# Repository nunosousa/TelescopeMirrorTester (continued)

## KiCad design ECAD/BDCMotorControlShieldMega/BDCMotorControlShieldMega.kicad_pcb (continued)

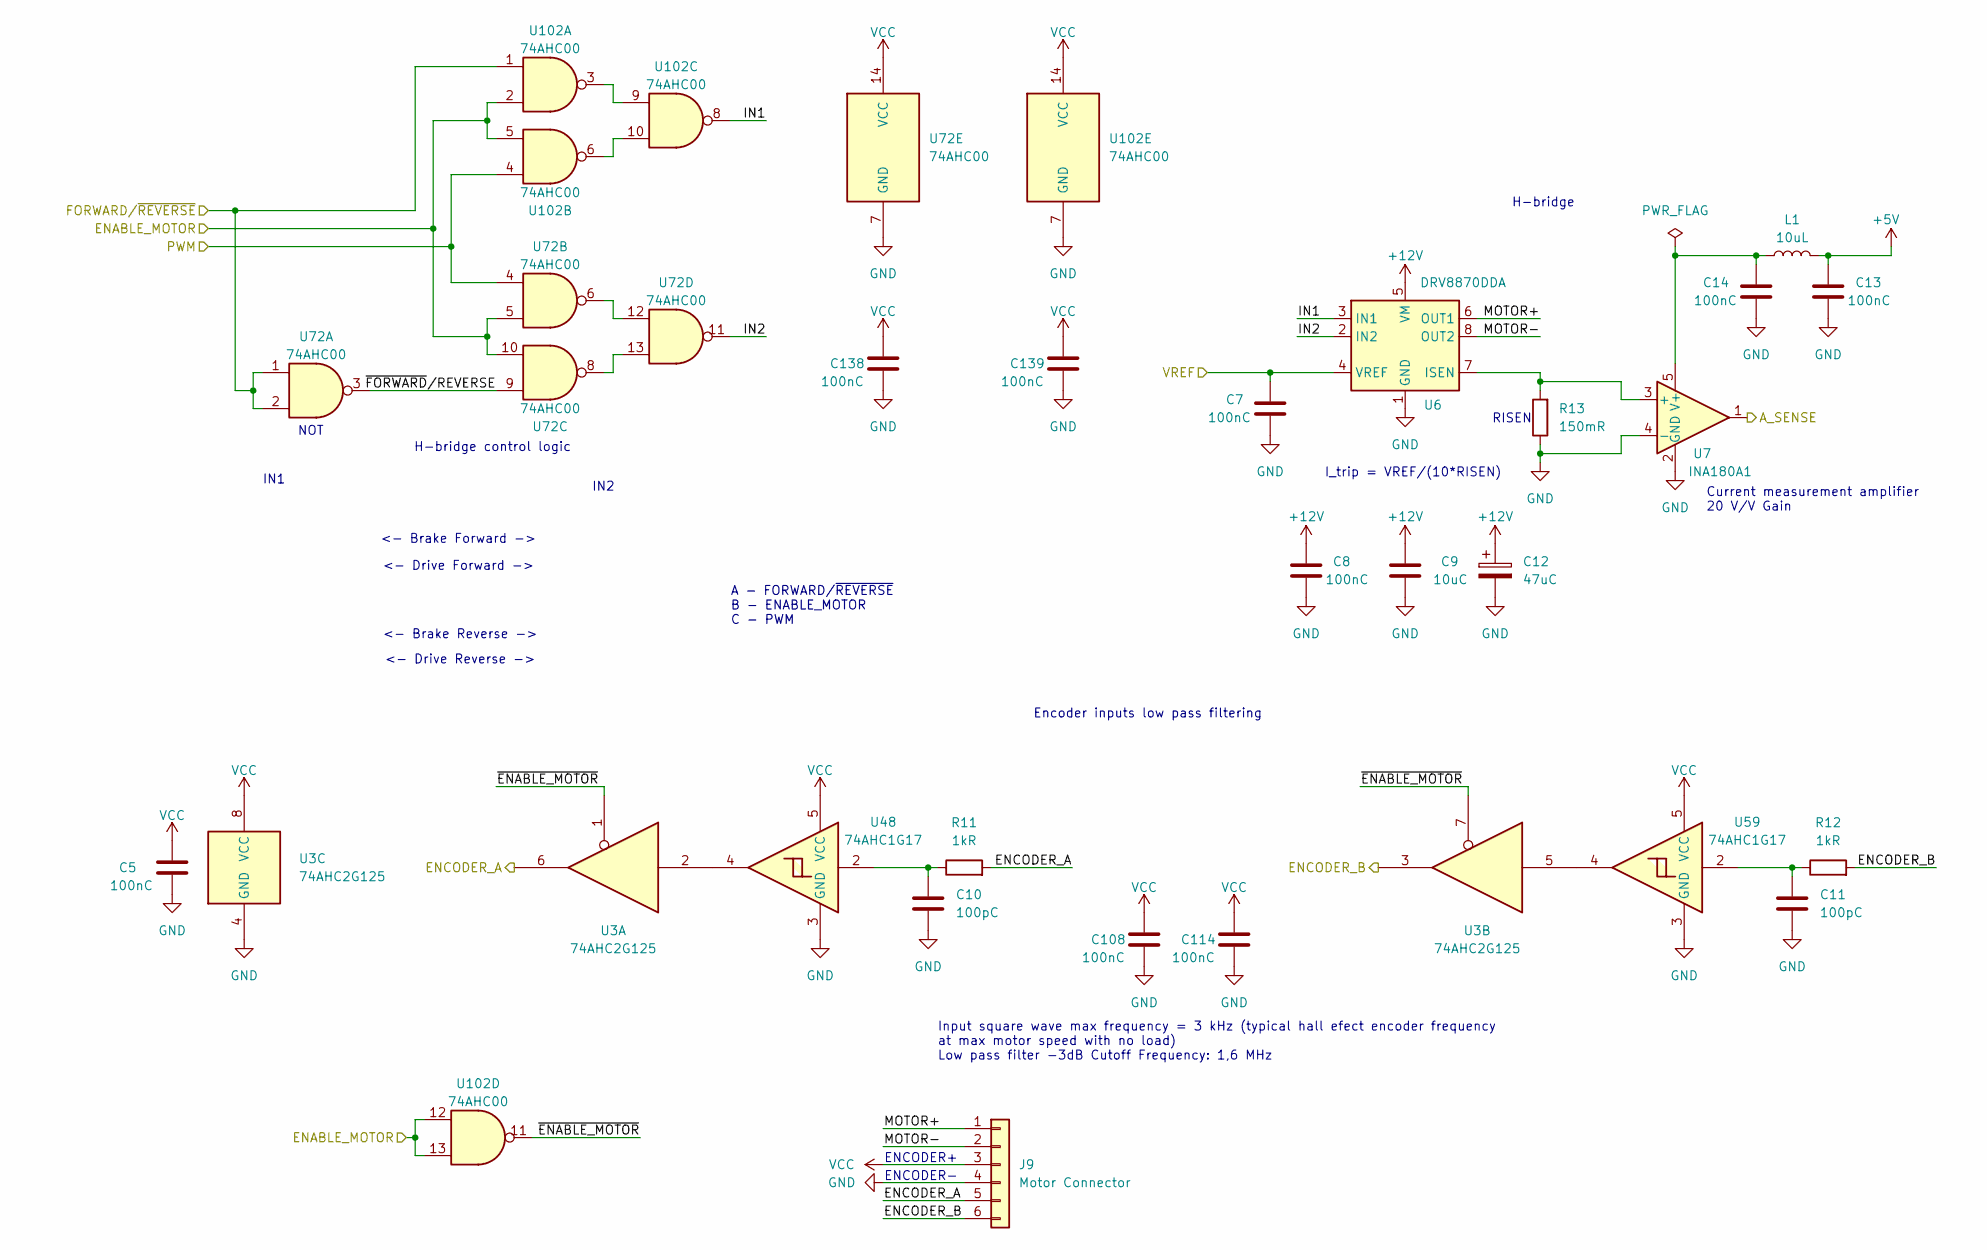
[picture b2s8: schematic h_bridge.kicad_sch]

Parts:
C5, C7, C8, C13, C14, C108, C114, C138, C139: 100nC; C_0805_2012Metric
C9: 10uC; C_1210_3225Metric; MPN UMK325AB7106KM-T
C10, C11: 100pC; C_0805_2012Metric; MPN CC0805KRX7R9BB101
C12: 47uC; CP_Radial_D5.0mm_P2.00mm; MPN 35YXJ47M5X11
J9: Motor Connector; JST_PH_B6B-PH-K_1x06_P2.00mm_Vertical; MPN B6B-PH-K-S(LF)(SN)
L1: 10uL; L_0805_2012Metric; MPN LQM21FN100M80L
R11, R12: 1kR; R_0805_2012Metric; MPN AC0805FR-7W1KL
R13: 150mR; R_1206_3216Metric; MPN RLH12FTCR150
U3: 74AHC2G125; TSSOP-8_3x3mm_P0.65mm; MPN 74AHC2G125DP,125
U6: DRV8870DDA; Texas_HTSOP-8-1EP_3.9x4.9mm_P1.27mm_EP2.95x4.9mm_Mask2.4x3.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; MPN DRV8870DDAR
U7: INA180A1; SOT-23-5; MPN INA180A1IDBVR
U48, U59: 74AHC1G17; SC-74A-5_1.55x2.9mm_P0.95mm; MPN 74AHC1G17GVH
U72, U102: 74AHC00; TSSOP-14_4.4x5mm_P0.65mm; MPN SN74AHC00PWR

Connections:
+5V: C13.1, L1.1; also elsewhere on the board
+12V: C8.1, C9.1, C12.1, U6.5 (VM); also elsewhere on the board
/*6: J9.6, R12.2, U3.3; also elsewhere on the board
/*7: J9.5, R11.2, U3.6; also elsewhere on the board
/*11: U72.4, U102.4; also elsewhere on the board
/Motor Control/CURRENT_M1A: U7.1; also elsewhere on the board
/Motor Control/EN_M1A: U72.5, U72.10, U102.2, U102.5, U102.12, U102.13; also elsewhere on the board
/Motor Control/F/~R_MA: U72.1, U72.2, U102.1; also elsewhere on the board
/Motor Control/H-bridge #1/IN1: U6.3 (IN1), U102.8
/Motor Control/H-bridge #1/IN2: U6.2 (IN2), U72.11
/Motor Control/H-bridge #1/MOTOR+: J9.1, U6.6 (OUT1)
/Motor Control/H-bridge #1/MOTOR-: J9.2, U6.8 (OUT2)
/Motor Control/H-bridge #1/~ENABLE_MOTOR: U3.1, U3.7, U102.11
/Motor Control/H-bridge #1/~FORWARD/REVERSE: U72.3, U72.9
/Motor Control/VREF_M1A: C7.1, U6.4 (VREF); also elsewhere on the board
GND: C5.2, C7.2, C8.2, C9.2, C10.2, C11.2, C12.2, C13.2, C14.2, C108.2, C114.2, C138.2, C139.2, J9.4, R13.1, U3.4 (GND), U6.1 (GND), U6.9 (GND), U7.2 (GND), U7.4 (-), U48.3 (GND), U59.3 (GND), U72.7 (GND), U102.7 (GND); also elsewhere on the board
unnamed: C10.1, R11.1, U48.2
unnamed: C11.1, R12.1, U59.2
unnamed: U3.2, U48.4
unnamed: U3.5, U59.4
unnamed: R13.2, U6.7 (ISEN), U7.3 (+)
unnamed: C14.1, L1.2, U7.5 (V+)
unnamed: U72.6, U72.12
unnamed: U72.8, U72.13
unnamed: U102.3, U102.9
unnamed: U102.6, U102.10
VCC: C5.1, C108.1, C114.1, C138.1, C139.1, J9.3, U3.8 (VCC), U48.5 (VCC), U59.5 (VCC), U72.14 (VCC), U102.14 (VCC); also elsewhere on the board

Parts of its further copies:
C20, C27, C28, C43, C44, C46, C53, C54, C62, C64, C68, C74, C75, C78, C79, C81, C87, C88, C91, C92, C94, C100, C101, C104, C105, C109, C110, C111, C112, C113, C115, C116, C117, C118, C119, C141, C142, C144, C145, C147, C148, C150, C151, C153, C154: 100nC; C_0805_2012Metric
C23, C24, C49, C50, C71, C72, C84, C85, C97, C98: 100pC; C_0805_2012Metric; MPN CC0805KRX7R9BB101
C29, C55, C76, C89, C102: 10uC; C_1210_3225Metric; MPN UMK325AB7106KM-T
C30, C61, C77, C90, C103: 47uC; CP_Radial_D5.0mm_P2.00mm; MPN 35YXJ47M5X11
J12, J15, J19, J20, J21: Motor Connector; JST_PH_B6B-PH-K_1x06_P2.00mm_Vertical; MPN B6B-PH-K-S(LF)(SN)
L2, L3, L5, L6, L7: 10uL; L_0805_2012Metric; MPN LQM21FN100M80L
R1, R2, R4, R9, R18, R19, R21, R22, R28, R29: 1kR; R_0805_2012Metric; MPN AC0805FR-7W1KL
R3, R10, R20, R27, R30: 150mR; R_1206_3216Metric; MPN RLH12FTCR150
U4, U8, U9, U19, U25: 74AHC2G125; TSSOP-8_3x3mm_P0.65mm; MPN 74AHC2G125DP,125
U17, U29, U37, U45, U52: DRV8870DDA; Texas_HTSOP-8-1EP_3.9x4.9mm_P1.27mm_EP2.95x4.9mm_Mask2.4x3.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; MPN DRV8870DDAR
U18, U30, U39, U46, U53: INA180A1; SOT-23-5; MPN INA180A1IDBVR
U54, U55, U56, U57, U58, U60, U61, U62, U63, U64: 74AHC1G17; SC-74A-5_1.55x2.9mm_P0.95mm; MPN 74AHC1G17GVH
U73, U74, U75, U76, U77, U103, U104, U105, U106, U107: 74AHC00; TSSOP-14_4.4x5mm_P0.65mm; MPN SN74AHC00PWR

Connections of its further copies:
+5V: C44.1, C64.1, C79.1, C92.1, C105.1, L2.1, L3.1, L5.1, L6.1, L7.1; also elsewhere on the board
+12V: C28.1, C29.1, C30.1, C54.1, C55.1, C61.1, C75.1, C76.1, C77.1, C88.1, C89.1, C90.1, C101.1, C102.1, C103.1, U17.5 (VM), U29.5 (VM), U37.5 (VM), U45.5 (VM), U52.5 (VM); also elsewhere on the board
/*4: J12.6, J19.6, J21.6, R2.2, R19.2, R29.2, U4.3, U9.3, U25.3; also elsewhere on the board
/*5: J12.5, J19.5, J21.5, R1.2, R18.2, R28.2, U4.6, U9.6, U25.6; also elsewhere on the board
/*6: J15.6, J20.6, R9.2, R22.2, U8.3, U19.3; also elsewhere on the board
/*7: J15.5, J20.5, R4.2, R21.2, U8.6, U19.6; also elsewhere on the board
/*11: U74.4, U76.4, U104.4, U106.4; also elsewhere on the board
/*13: U73.4, U75.4, U77.4, U103.4, U105.4, U107.4; also elsewhere on the board
/Motor Control/CURRENT_M1B: U18.1; also elsewhere on the board
/Motor Control/CURRENT_M2A: U30.1; also elsewhere on the board
/Motor Control/CURRENT_M2B: U39.1; also elsewhere on the board
/Motor Control/CURRENT_M3A: U46.1; also elsewhere on the board
/Motor Control/CURRENT_M3B: U53.1; also elsewhere on the board
/Motor Control/EN_M1B: U73.5, U73.10, U103.2, U103.5, U103.12, U103.13; also elsewhere on the board
/Motor Control/EN_M2A: U74.5, U74.10, U104.2, U104.5, U104.12, U104.13; also elsewhere on the board
/Motor Control/EN_M2B: U75.5, U75.10, U105.2, U105.5, U105.12, U105.13; also elsewhere on the board
/Motor Control/EN_M3A: U76.5, U76.10, U106.2, U106.5, U106.12, U106.13; also elsewhere on the board
/Motor Control/EN_M3B: U77.5, U77.10, U107.2, U107.5, U107.12, U107.13; also elsewhere on the board
/Motor Control/F/~R_MA: U74.1, U74.2, U76.1, U76.2, U104.1, U106.1; also elsewhere on the board
/Motor Control/F/~R_MB: U73.1, U73.2, U75.1, U75.2, U77.1, U77.2, U103.1, U105.1, U107.1; also elsewhere on the board
/Motor Control/H-bridge #2/IN1: U17.3 (IN1), U103.8
/Motor Control/H-bridge #2/IN2: U17.2 (IN2), U73.11
/Motor Control/H-bridge #2/MOTOR+: J12.1, U17.6 (OUT1)
/Motor Control/H-bridge #2/MOTOR-: J12.2, U17.8 (OUT2)
/Motor Control/H-bridge #2/~ENABLE_MOTOR: U4.1, U4.7, U103.11
/Motor Control/H-bridge #2/~FORWARD/REVERSE: U73.3, U73.9
/Motor Control/H-bridge #3/IN1: U29.3 (IN1), U104.8
/Motor Control/H-bridge #3/IN2: U29.2 (IN2), U74.11
/Motor Control/H-bridge #3/MOTOR+: J15.1, U29.6 (OUT1)
/Motor Control/H-bridge #3/MOTOR-: J15.2, U29.8 (OUT2)
/Motor Control/H-bridge #3/~ENABLE_MOTOR: U8.1, U8.7, U104.11
/Motor Control/H-bridge #3/~FORWARD/REVERSE: U74.3, U74.9
/Motor Control/H-bridge #4/IN1: U37.3 (IN1), U105.8
/Motor Control/H-bridge #4/IN2: U37.2 (IN2), U75.11
/Motor Control/H-bridge #4/MOTOR+: J19.1, U37.6 (OUT1)
/Motor Control/H-bridge #4/MOTOR-: J19.2, U37.8 (OUT2)
/Motor Control/H-bridge #4/~ENABLE_MOTOR: U9.1, U9.7, U105.11
/Motor Control/H-bridge #4/~FORWARD/REVERSE: U75.3, U75.9
/Motor Control/H-bridge #5/IN1: U45.3 (IN1), U106.8
/Motor Control/H-bridge #5/IN2: U45.2 (IN2), U76.11
/Motor Control/H-bridge #5/MOTOR+: J20.1, U45.6 (OUT1)
/Motor Control/H-bridge #5/MOTOR-: J20.2, U45.8 (OUT2)
/Motor Control/H-bridge #5/~ENABLE_MOTOR: U19.1, U19.7, U106.11
/Motor Control/H-bridge #5/~FORWARD/REVERSE: U76.3, U76.9
/Motor Control/H-bridge #6/IN1: U52.3 (IN1), U107.8
/Motor Control/H-bridge #6/IN2: U52.2 (IN2), U77.11
/Motor Control/H-bridge #6/MOTOR+: J21.1, U52.6 (OUT1)
/Motor Control/H-bridge #6/MOTOR-: J21.2, U52.8 (OUT2)
/Motor Control/H-bridge #6/~ENABLE_MOTOR: U25.1, U25.7, U107.11
/Motor Control/H-bridge #6/~FORWARD/REVERSE: U77.3, U77.9
/Motor Control/VREF_M1B: C27.1, U17.4 (VREF); also elsewhere on the board
/Motor Control/VREF_M2A: C53.1, U29.4 (VREF); also elsewhere on the board
/Motor Control/VREF_M2B: C74.1, U37.4 (VREF); also elsewhere on the board
/Motor Control/VREF_M3A: C87.1, U45.4 (VREF); also elsewhere on the board
/Motor Control/VREF_M3B: C100.1, U52.4 (VREF); also elsewhere on the board
GND: C20.2, C23.2, C24.2, C27.2, C28.2, C29.2, C30.2, C43.2, C44.2, C46.2, C49.2, C50.2, C53.2, C54.2, C55.2, C61.2, C62.2, C64.2, C68.2, C71.2, C72.2, C74.2, C75.2, C76.2, C77.2, C78.2, C79.2, C81.2, C84.2, C85.2, C87.2, C88.2, C89.2, C90.2, C91.2, C92.2, C94.2, C97.2, C98.2, C100.2, C101.2, C102.2, C103.2, C104.2, C105.2, C109.2, C110.2, C111.2, C112.2, C113.2, C115.2, C116.2, C117.2, C118.2, C119.2, C141.2, C142.2, C144.2, C145.2, C147.2, C148.2, C150.2, C151.2, C153.2, C154.2, J12.4, J15.4, J19.4, J20.4, J21.4, R3.1, R10.1, R20.1, R27.1, R30.1, U4.4 (GND), U8.4 (GND), U9.4 (GND), U17.1 (GND), U17.9 (GND), U18.2 (GND), U18.4 (-), U19.4 (GND), U25.4 (GND), U29.1 (GND), U29.9 (GND), U30.2 (GND), U30.4 (-), U37.1 (GND), U37.9 (GND), U39.2 (GND), U39.4 (-), U45.1 (GND), U45.9 (GND), U46.2 (GND), U46.4 (-), U52.1 (GND), U52.9 (GND), U53.2 (GND), U53.4 (-), U54.3 (GND), U55.3 (GND), U56.3 (GND), U57.3 (GND), U58.3 (GND), U60.3 (GND), U61.3 (GND), U62.3 (GND), U63.3 (GND), U64.3 (GND), U73.7 (GND), U74.7 (GND), U75.7 (GND), U76.7 (GND), U77.7 (GND), U103.7 (GND), U104.7 (GND), U105.7 (GND), U106.7 (GND), U107.7 (GND); also elsewhere on the board
unnamed: C23.1, R1.1, U54.2
unnamed: C24.1, R2.1, U60.2
unnamed: C49.1, R4.1, U55.2
unnamed: C50.1, R9.1, U61.2
unnamed: C71.1, R18.1, U56.2
unnamed: C72.1, R19.1, U62.2
unnamed: C84.1, R21.1, U57.2
unnamed: C85.1, R22.1, U63.2
unnamed: C97.1, R28.1, U58.2
unnamed: C98.1, R29.1, U64.2
unnamed: U4.2, U54.4
unnamed: U4.5, U60.4
unnamed: R3.2, U17.7 (ISEN), U18.3 (+)
unnamed: C43.1, L2.2, U18.5 (V+)
unnamed: U19.2, U57.4
unnamed: U19.5, U63.4
unnamed: U25.2, U58.4
unnamed: U25.5, U64.4
unnamed: R10.2, U29.7 (ISEN), U30.3 (+)
unnamed: C62.1, L3.2, U30.5 (V+)
unnamed: R20.2, U37.7 (ISEN), U39.3 (+)
unnamed: C78.1, L5.2, U39.5 (V+)
unnamed: R27.2, U45.7 (ISEN), U46.3 (+)
unnamed: C91.1, L6.2, U46.5 (V+)
unnamed: R30.2, U52.7 (ISEN), U53.3 (+)
unnamed: C104.1, L7.2, U53.5 (V+)
unnamed: U8.2, U55.4
unnamed: U9.2, U56.4
unnamed: U8.5, U61.4
unnamed: U9.5, U62.4
unnamed: U73.6, U73.12
unnamed: U73.8, U73.13
unnamed: U74.6, U74.12
unnamed: U74.8, U74.13
unnamed: U75.6, U75.12
unnamed: U75.8, U75.13
unnamed: U76.6, U76.12
unnamed: U76.8, U76.13
unnamed: U77.6, U77.12
unnamed: U77.8, U77.13
unnamed: U103.3, U103.9
unnamed: U103.6, U103.10
unnamed: U104.3, U104.9
unnamed: U104.6, U104.10
unnamed: U105.3, U105.9
unnamed: U105.6, U105.10
unnamed: U106.3, U106.9
unnamed: U106.6, U106.10
unnamed: U107.3, U107.9
unnamed: U107.6, U107.10
VCC: C20.1, C46.1, C68.1, C81.1, C94.1, C109.1, C110.1, C111.1, C112.1, C113.1, C115.1, C116.1, C117.1, C118.1, C119.1, C141.1, C142.1, C144.1, C145.1, C147.1, C148.1, C150.1, C151.1, C153.1, C154.1, J12.3, J15.3, J19.3, J20.3, J21.3, U4.8 (VCC), U8.8 (VCC), U9.8 (VCC), U19.8 (VCC), U25.8 (VCC), U54.5 (VCC), U55.5 (VCC), U56.5 (VCC), U57.5 (VCC), U58.5 (VCC), U60.5 (VCC), U61.5 (VCC), U62.5 (VCC), U63.5 (VCC), U64.5 (VCC), U73.14 (VCC), U74.14 (VCC), U75.14 (VCC), U76.14 (VCC), U77.14 (VCC), U103.14 (VCC), U104.14 (VCC), U105.14 (VCC), U106.14 (VCC), U107.14 (VCC); also elsewhere on the board

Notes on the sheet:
<- Brake Forward ->
RISEN
H-bridge control logic
ENCODER+
IN2
Input square wave max frequency = 3 kHz (typical hall efect encoder frequency at max motor speed with no load) Low pass filter -3dB Cutoff Frequency: 1,6 MHz
IN1
Current measurement amplifier 20 V/V Gain
ENCODER-
NOT
Encoder inputs low pass filtering
I_trip = VREF/(10*RISEN)
<- Drive Reverse ->
<- Drive Forward ->
A - FORWARD/~{REVERSE} B - ENABLE_MOTOR C - PWM
H-bridge
<- Brake Reverse ->

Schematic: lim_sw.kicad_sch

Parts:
C6, C15, C16, C17, C18, C19, C21, C22, C26, C41, C42, C52: 100nC; C_0805_2012Metric
J10, J11, J13, J14, J16, J17: Limit switch; JST_PH_B2B-PH-K_1x02_P2.00mm_Vertical; MPN B2B-PH-K-S(LF)(SN)
R14, R15, R16, R17, R23, R24, R25, R26, R32, R33, R34, R35: 10kR; R_0805_2012Metric; MPN RC0805JR-0710KL
U10, U11, U15, U16, U26, U27: 74AHC1G17; SC-74A-5_1.55x2.9mm_P0.95mm; MPN 74AHC1G17GVH

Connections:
+5V: C6.1, C15.1, C18.1, C19.1, C21.1, C22.1, R16.2, R17.2, R24.2, R33.2, R34.2, R35.2, U10.5 (VCC), U11.5 (VCC), U15.5 (VCC), U16.5 (VCC), U26.5 (VCC), U27.5 (VCC); also elsewhere on the board
/Motor Control/LIM_SW00: U10.4; also elsewhere on the board
/Motor Control/LIM_SW01: U11.4; also elsewhere on the board
/Motor Control/LIM_SW02: U15.4; also elsewhere on the board
/Motor Control/LIM_SW03: U16.4; also elsewhere on the board
/Motor Control/LIM_SW04: U26.4; also elsewhere on the board
/Motor Control/LIM_SW05: U27.4; also elsewhere on the board
GND: C6.2, C15.2, C16.2, C17.2, C18.2, C19.2, C21.2, C22.2, C26.2, C41.2, C42.2, C52.2, J10.2, J11.2, J13.2, J14.2, J16.2, J17.2, U10.3 (GND), U11.3 (GND), U15.3 (GND), U16.3 (GND), U26.3 (GND), U27.3 (GND); also elsewhere on the board
unnamed: C16.1, R14.1, U10.2
unnamed: C17.1, R15.1, U11.2
unnamed: C26.1, R23.1, U15.2
unnamed: C41.1, R25.1, U16.2
unnamed: C42.1, R26.1, U26.2
unnamed: C52.1, R32.1, U27.2
unnamed: J10.1, R14.2, R16.1
unnamed: J11.1, R15.2, R17.1
unnamed: J13.1, R23.2, R24.1
unnamed: J14.1, R25.2, R33.1
unnamed: J16.1, R26.2, R34.1
unnamed: J17.1, R32.2, R35.1

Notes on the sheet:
Limit switches debouncing

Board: 2 copper layers, 279 parts (0 on the bottom side), 236 nets, no tracks yet.

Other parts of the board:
MH1, MH2, MH3, MH4, MH5, MH6: MountingHole_3.2mm
kibuzzard-68938B3A: G***; kibuzzard-68938B3A
kibuzzard-68938B4A: G***; kibuzzard-68938B4A
kibuzzard-68938B20: G***; kibuzzard-68938B20
kibuzzard-68938B29: G***; kibuzzard-68938B29
kibuzzard-68938B31: G***; kibuzzard-68938B31
kibuzzard-68938B43: G***; kibuzzard-68938B43

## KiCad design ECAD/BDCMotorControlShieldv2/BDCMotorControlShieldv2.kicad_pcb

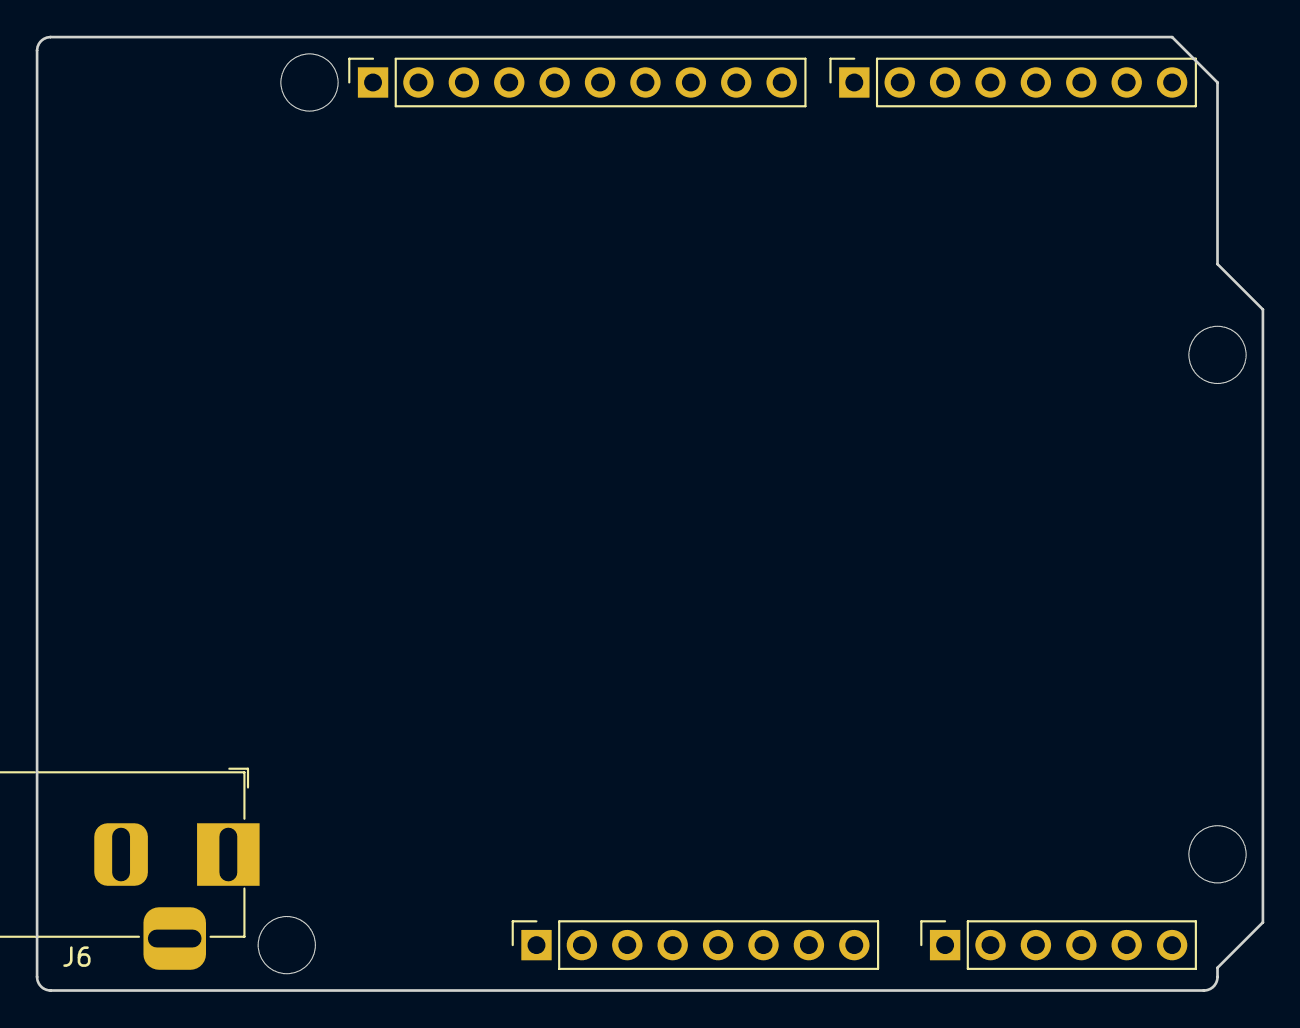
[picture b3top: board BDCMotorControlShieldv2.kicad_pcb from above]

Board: 4 copper layers, 68.6 x 53.3 mm, 9 parts (0 on the bottom side), 3 nets, no tracks yet.

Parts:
J1: Power; PinSocket_1x08_P2.54mm_Vertical
J2: Digital/PWM; PinSocket_1x10_P2.54mm_Vertical
J3: Analog; PinSocket_1x06_P2.54mm_Vertical
J4: Digital/PWM; PinSocket_1x08_P2.54mm_Vertical
J6: Barrel_Jack_Switch; BarrelJack_Horizontal
MH1, MH2, MH3, MH4: MountingHole_3.2mm

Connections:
/SCL/A5: J2.1, J3.6
/SDA/A4: J2.2, J3.5
GND: J1.6, J1.7, J2.4, J6.2, J6.3

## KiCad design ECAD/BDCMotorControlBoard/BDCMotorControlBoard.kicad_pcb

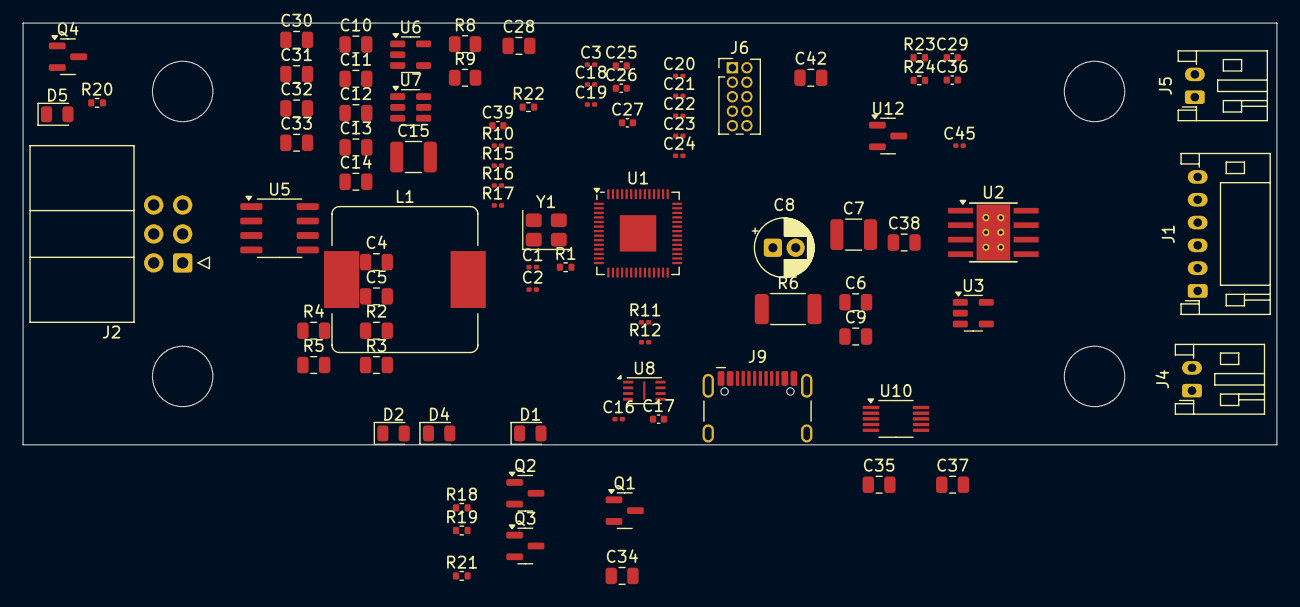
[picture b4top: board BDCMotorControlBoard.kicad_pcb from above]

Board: 4 copper layers, 110.0 x 37.0 mm, 91 parts (0 on the bottom side), 51 nets, no tracks yet.

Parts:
C1, C2: 15pC; C_0201_0603Metric
C3, C16, C18, C19, C20, C21, C22, C23, C24, C45: 100nC; C_0201_0603Metric
C4, C5, C6, C9, C10, C13, C30, C32, C34, C35, C38, C42: 100nC; C_0805_2012Metric
C7: 10uC; C_1210_3225Metric
C8: 47uC; CP_Radial_D5.0mm_P2.00mm
C11, C12, C28, C31, C33, C37: 10uC; C_0805_2012Metric
C14: C; C_0805_2012Metric
C15: C; C_1210_3225Metric
C17, C25, C26, C27: 2u2C; C_0402_1005Metric
C29, C36, C39: 100pC; C_0402_1005Metric
D1, D2, D4, D5: LED; LED_0805_2012Metric
H1, H2, H3, H4: MountingHole; MountingHole_5.3mm_M5
J1: Motor Connector; JST_PH_S6B-PH-K_1x06_P2.00mm_Horizontal
J2: RS485 PCB; IDC-Header_2x03_P2.54mm_Horizontal
J4, J5: Limit switch; JST_PH_S2B-PH-K_1x02_P2.00mm_Horizontal
J6: Conn_ARM_JTAG_SWD_10; PinHeader_2x05_P1.27mm_Vertical
J9: USB_C_Receptacle_USB2.0_16P; USB_C_Receptacle_HCTL_HC-TYPE-C-16P-01A
L1: L; L_TaiTech_TMPC1265_13.5x12.5mm
Q1, Q2, Q3, Q4: BC847; SOT-23
R1, R22, R23, R24: 1kR; R_0402_1005Metric
R2, R3, R4, R5: 10kR; C_0805_2012Metric
R6: R; R_2010_5025Metric
R8, R9: R; R_0805_2012Metric
R10, R15, R16, R17: 100R; R_0201_0603Metric
R11, R12: 27R; R_0201_0603Metric
R18, R19, R20, R21: 5k1R; R_0402_1005Metric
U1: RP2040; QFN-56-1EP_7x7mm_P0.4mm_EP3.2x3.2mm
U2: DRV8870DDA; Texas_HTSOP-8-1EP_3.9x4.9mm_P1.27mm_EP2.95x4.9mm_Mask2.4x3.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
U3: INA180A1; SOT-23-5
U5: SP3485EN; SOIC-8_3.9x4.9mm_P1.27mm
U6: TLV75533PDBV; SOT-23-5
U7: TPS54202DDC; SOT-23-6
U8: W25Q16JVUXIQ; Winbond_USON-8-1EP_3x2mm_P0.5mm_EP0.2x1.6mm
U10: PGA112; VSSOP-10_3x3mm_P0.5mm
U12: REF3033; SOT-23
Y1: ABM8-272-T3; Crystal_SMD_3225-4Pin_3.2x2.5mm

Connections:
+1V1: C3.1, C19.1, C25.1, U1.23 (DVDD), U1.45 (VREG_VOUT), U1.50 (DVDD)
+3.3V: C16.1, C17.1, C18.1, C20.1, C21.1, C22.1, C23.1, C24.1, C26.1, C28.1, C34.1, C35.1, C37.1, C45.1, J1.3, J6.1 (VTref), R3.2, R5.2, R10.1, R15.1, R16.1, R17.1, U1.1 (IOVDD), U1.10 (IOVDD), U1.22 (IOVDD), U1.33 (IOVDD), U1.42 (IOVDD), U1.44 (VREG_IN), U1.48 (USB_VDD), U1.49 (IOVDD), U5.8 (VCC), U6.5 (OUT), U8.8 (VCC)
+3.3VA: C9.1, C27.1, C38.1, C42.1, U1.43 (ADC_AVDD), U2.4 (VREF), U3.5 (V+), U10.1 (AV_{DD}), U10.3 (CH0/V_{CAL}), U10.10 (DV_{DD}), U12.2 (OUT)
+12V: C6.1, C7.1, C8.1, C10.1, C11.1, C12.1, J2.5, J2.6, U2.5 (VM), U7.3 (VIN), U7.5 (EN)
/MCU/GPIO26_ADC0: C39.1, R22.1, U1.38 (GPIO26_ADC0)
/MCU/MOTOR_A_SENSE: R22.2, U10.5 (V_{OUT})
/MCU/MOTOR_LIM1: C4.1, R2.1
/MCU/MOTOR_LIM2: C5.1, R4.1
/MCU/QSPI_SCLK: U1.52 (QSPI_SCLK), U8.6 (CLK)
/MCU/QSPI_SD0: U1.53 (QSPI_SD0), U8.5 (DI/IO_{0})
/MCU/QSPI_SD1: U1.55 (QSPI_SD1), U8.2 (DO/IO_{1})
/MCU/QSPI_SD2: U1.54 (QSPI_SD2), U8.3 (~WP/IO_{2})
/MCU/QSPI_SD3: U1.51 (QSPI_SD3), U8.7 (~HOLD/~RESET/IO_{3})
/MCU/QSPI_SS: U1.56 (QSPI_SS), U8.1 (~CS)
/MCU/RUN: J6.10 (~RESET), U1.26 (RUN)
/MCU/SWCLK: J6.4 (SWCLK/TCK), U1.24 (SWCLK)
/MCU/SWD: J6.2 (SWDIO/TMS), U1.25 (SWD)
/MCU/USB_D+: R12.2, U1.47 (USB_DP)
/MCU/USB_D-: R11.2, U1.46 (USB_DM)
/MCU/XIN: C1.2, U1.20 (XIN), Y1.1
/MCU/XOUT: R1.2, U1.21 (XOUT)
/Motor Control/A_SENSE_BASE: U3.1, U10.2 (CH1)
/Motor Control/ENCODER_A: C29.1, J1.5, R23.1, R23.2
/Motor Control/ENCODER_B: C36.1, J1.6, R24.1, R24.2
/Motor Control/MOTOR+: J1.1, U2.6 (OUT1)
/Motor Control/MOTOR-: J1.2, U2.8 (OUT2)
/RS485/RS485_N: J2.2, U5.7 (B)
/RS485/RS485_P: J2.1, U5.6 (A)
GND: C1.1, C2.1, C3.2, C4.2, C5.2, C6.2, C7.2, C8.2, C9.2, C10.2, C11.2, C12.2, C15.2, C16.2, C17.2, C18.2, C19.2, C20.2, C21.2, C22.2, C23.2, C24.2, C25.2, C26.2, C27.2, C28.2, C29.2, C30.2, C31.2, C32.2, C33.2, C34.2, C35.2, C36.2, C37.2, C38.2, C39.2, C42.2, C45.2, J1.4, J2.3, J2.4, J4.2, J5.2, J6.3 (GND), J6.5 (GND), J6.9 (GNDDetect), J9.A1 (GND), J9.A12 (GND), J9.B1 (GND), J9.B12 (GND), J9.S1 (SHIELD), Q1.2 (E), Q2.2 (E), Q3.2 (E), Q4.2 (E), R6.2, R8.2, U1.19 (TESTEN), U1.57 (GND), U2.1 (GND), U2.9 (GND), U3.2 (GND), U3.4 (-), U5.5 (GND), U6.2 (GND), U7.1 (GND), U8.4 (GND), U10.4 (V_{REF}), U10.6 (GND), U12.3 (GND), Y1.2, Y1.4
unnamed: C2.2, R1.1, Y1.3
unnamed: D1.2 (A), R15.2
unnamed: D1.1 (K), Q3.3 (C)
unnamed: D2.2 (A), R16.2
unnamed: D2.1 (K), Q2.3 (C)
unnamed: D4.2 (A), R17.2
unnamed: D4.1 (K), Q1.3 (C)
unnamed: D5.2 (A), R10.2
unnamed: D5.1 (K), Q4.3 (C)
unnamed: J4.1, R2.2, R3.1
unnamed: J5.1, R4.2, R5.1
unnamed: J9.A6 (D+), J9.B6 (D+), R12.1
unnamed: J9.A7 (D-), J9.B7 (D-), R11.1
unnamed: Q1.1 (B), R18.1
unnamed: Q2.1 (B), R19.1
unnamed: Q3.1 (B), R21.1
unnamed: Q4.1 (B), R20.1
unnamed: R6.1, U2.7 (ISEN), U3.3 (+)
unnamed: C13.1, U7.6 (BOOT)
unnamed: C14.2, R8.1, R9.2, U7.4 (FB)
unnamed: C13.2, L1.1, U7.2 (SW)
unnamed: C14.1, C15.1, C30.1, C31.1, C32.1, C33.1, L1.2, R9.1, U6.1 (IN), U6.3 (EN), U12.1 (IN)

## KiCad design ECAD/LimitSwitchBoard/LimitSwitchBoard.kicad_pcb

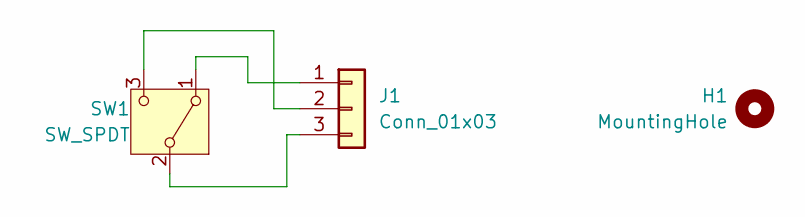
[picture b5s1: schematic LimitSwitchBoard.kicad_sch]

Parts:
H1: MountingHole; MountingHole_5.3mm_M5
J1: Conn_01x03; PinSocket_1x03_P2.00mm_Vertical
SW1: SW_SPDT; SS075Q102F035V2A

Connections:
unnamed: J1.1, SW1.1 (A)
unnamed: J1.2, SW1.3 (C)
unnamed: J1.3, SW1.2 (B)

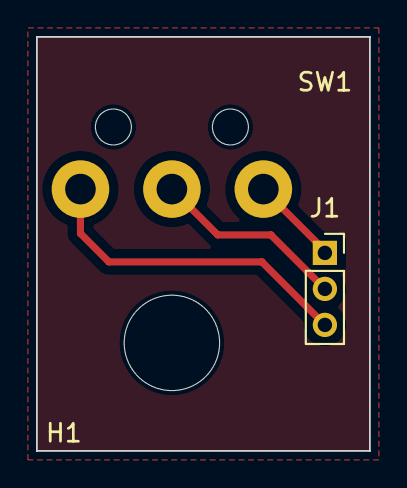
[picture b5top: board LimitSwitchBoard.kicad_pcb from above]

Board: 2 copper layers, 18.5 x 23.0 mm, 3 parts (0 on the bottom side), 3 nets.

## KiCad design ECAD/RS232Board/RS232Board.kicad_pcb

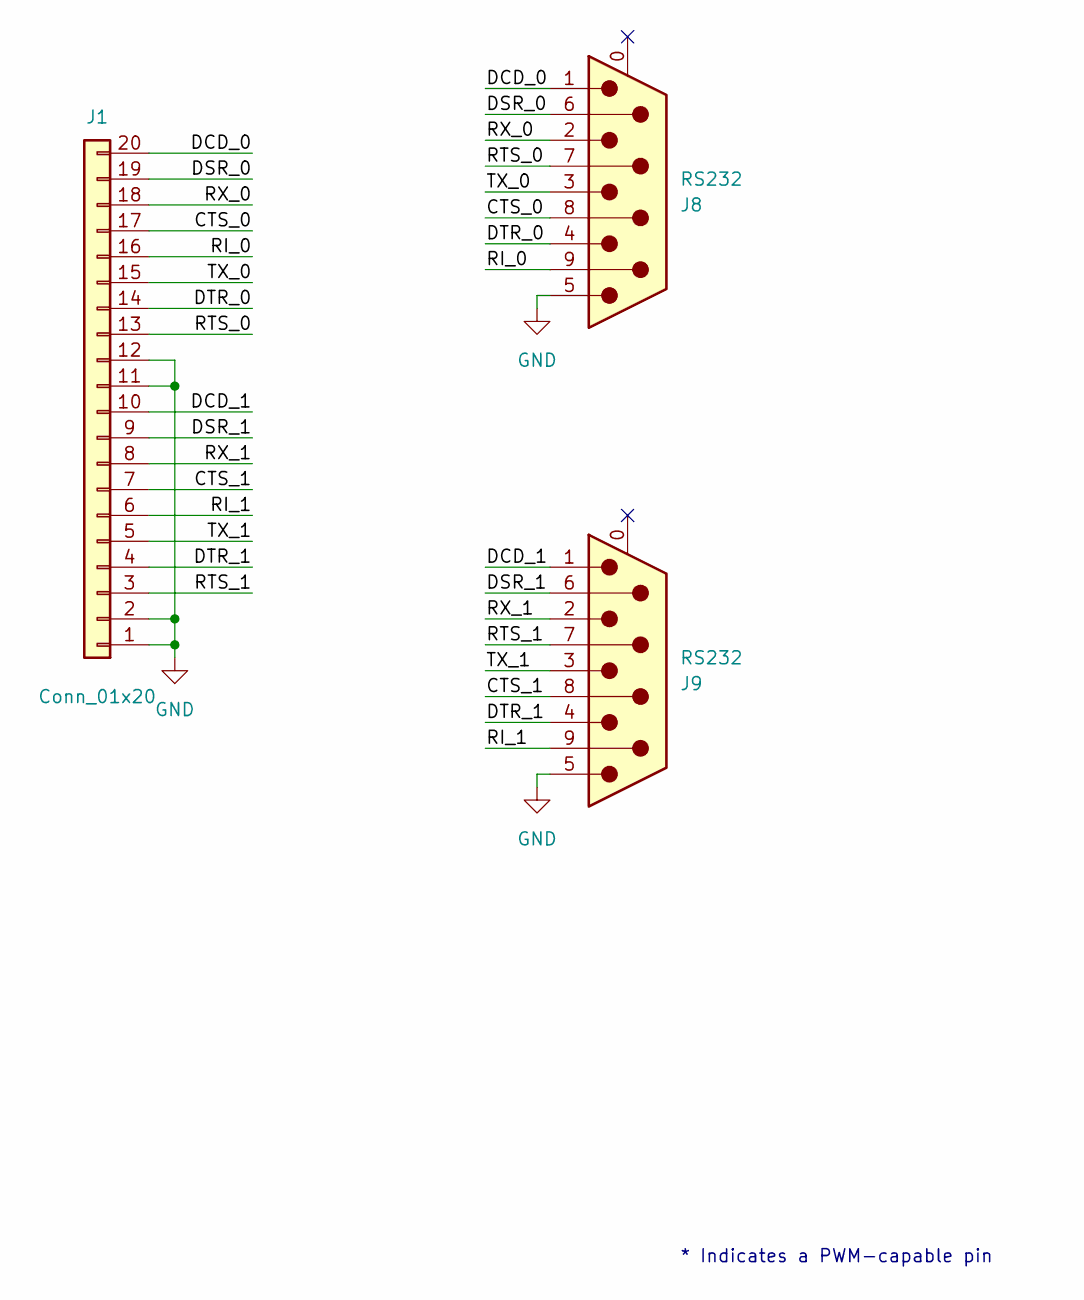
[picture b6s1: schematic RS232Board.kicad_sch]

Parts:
J1: Conn_01x20; TE_2-84952-0_1x20-1MP_P1.0mm_Horizontal; MPN CT10252-20R-00-D
J8, J9: RS232; DSUB-9_Male_Horizontal_P2.77x2.84mm_EdgePinOffset4.94mm_Hou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; MPN DT10121-M5W3-4F

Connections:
/CTS_0: J1.17, J8.8
/CTS_1: J1.7, J9.8
/DCD_0: J1.20, J8.1
/DCD_1: J1.10, J9.1
/DSR_0: J1.19, J8.6
/DSR_1: J1.9, J9.6
/DTR_0: J1.14, J8.4
/DTR_1: J1.4, J9.4
/RI_0: J1.16, J8.9
/RI_1: J1.6, J9.9
/RTS_0: J1.13, J8.7
/RTS_1: J1.3, J9.7
/RX_0: J1.18, J8.2
/RX_1: J1.8, J9.2
/TX_0: J1.15, J8.3
/TX_1: J1.5, J9.3
GND: J1.1, J1.2, J1.11, J1.12, J8.5, J9.5

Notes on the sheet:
* Indicates a PWM-capable pin

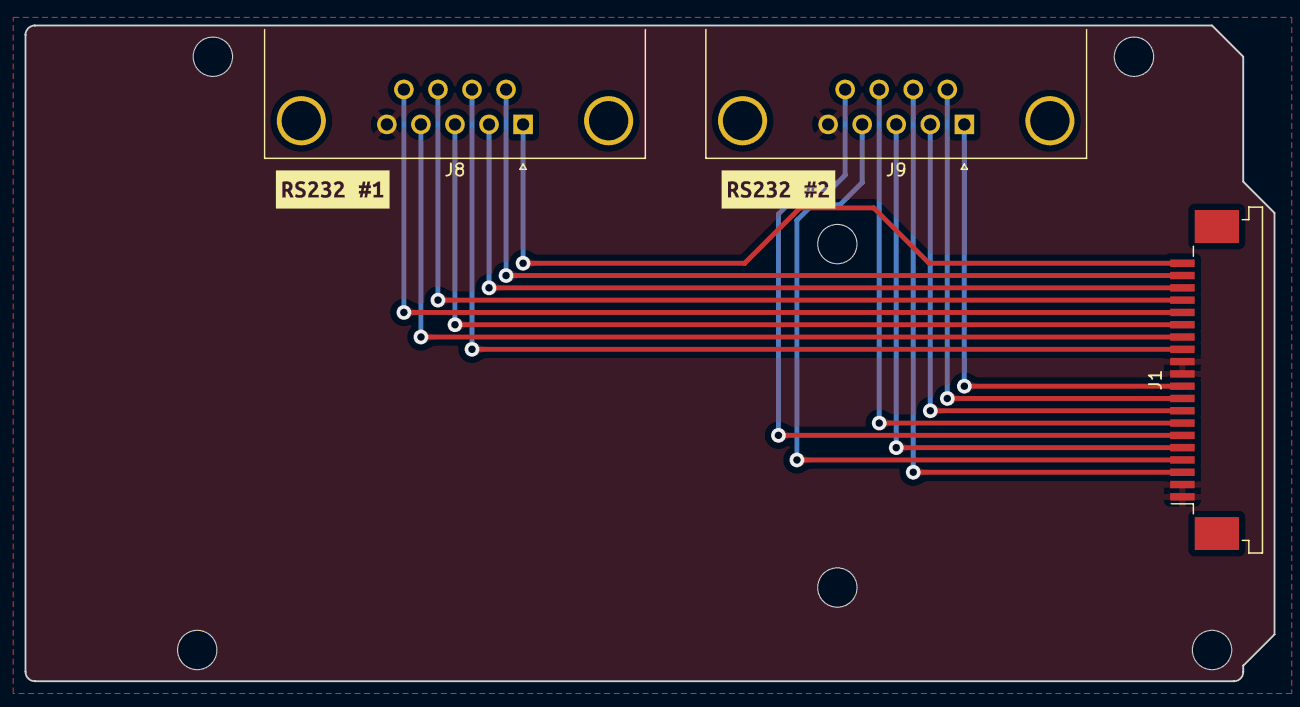
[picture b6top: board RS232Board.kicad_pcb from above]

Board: 2 copper layers, 101.6 x 53.3 mm, 11 parts (0 on the bottom side), 17 nets.

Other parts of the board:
MH1, MH2, MH3, MH4, MH5, MH6: MountingHole_3.2mm
kibuzzard-66E5B9FC: G***; kibuzzard-66E5B9FC
kibuzzard-66E5BA0D: G***; kibuzzard-66E5BA0D

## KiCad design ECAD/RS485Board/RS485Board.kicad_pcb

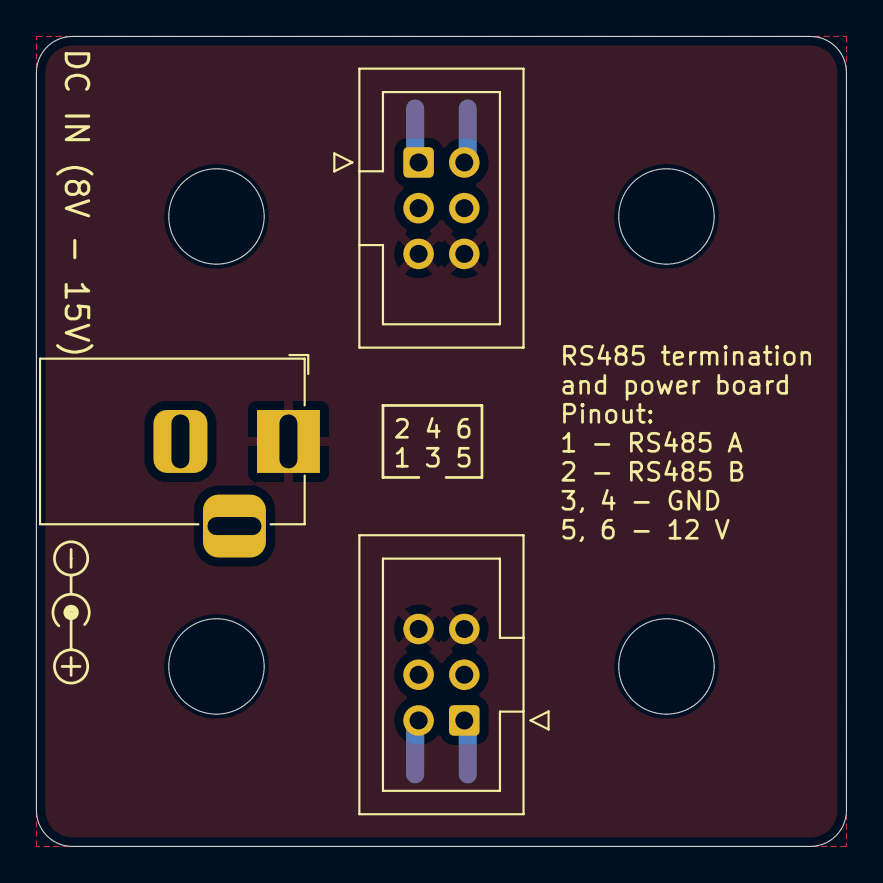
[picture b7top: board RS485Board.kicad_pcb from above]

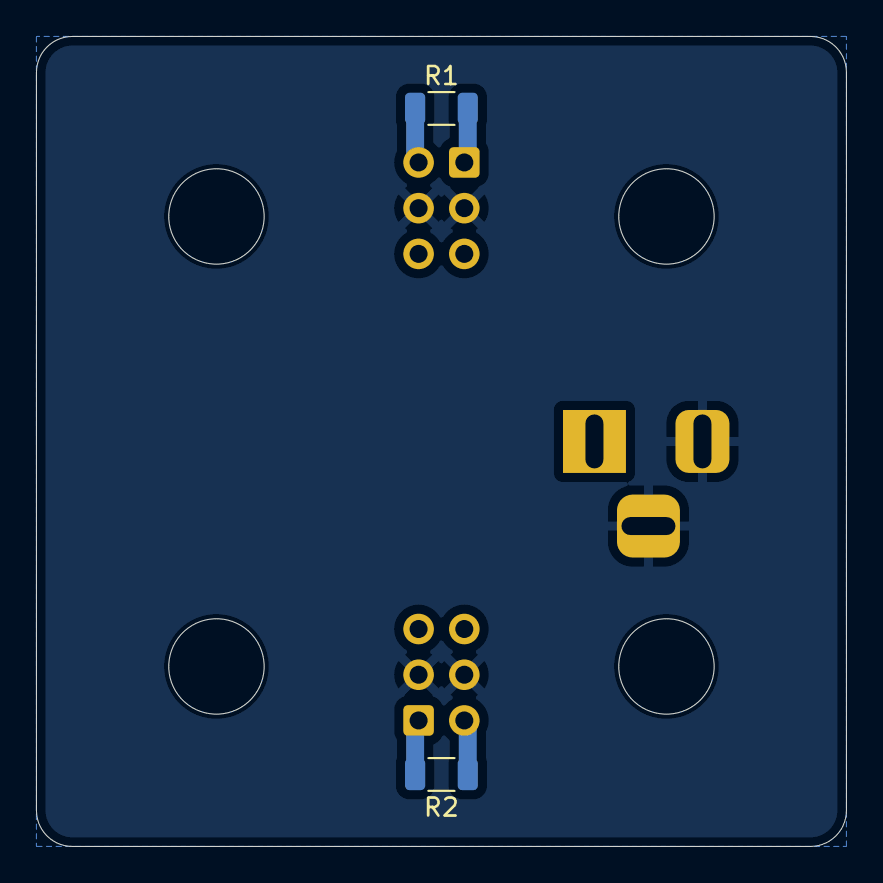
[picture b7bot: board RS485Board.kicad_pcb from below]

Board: 2 copper layers, 45.0 x 45.0 mm, 9 parts (2 on the bottom side), 6 nets.

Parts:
H1, H2, H3, H4: MountingHole; MountingHole_5.3mm_M5
J1, J2: RS485; IDC-Header_2x03_P2.54mm_Vertical
J3: Barrel_Jack_Switch; BarrelJack_Horizontal
R1, R2: 120R; R_1206_3216Metric

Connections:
+12V: J1.5, J1.6, J2.5, J2.6, J3.1
GND: J1.3, J1.4, J2.3, J2.4, J3.2, J3.3
unnamed: J1.1, R1.2
unnamed: J1.2, R1.1
unnamed: J2.1, R2.2
unnamed: J2.2, R2.1
